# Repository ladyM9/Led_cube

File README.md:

# Led_cube(8x8x8)
This project is based on the STM32F103C8T6 (Blue Pill) for controlling WS2812D (LED diodes). The LED cube is used for ambient lighting.
Various animations can be displayed on the LED cube, which makes it very impressive and interesting.

## ***How this project works***

The STM32F103C8T6 and WS2812D (LED diodes) cannot be directly connected because they operate at different voltage levels. 
To solve this issue, the LED diodes and STM32F103C8T6 are connected using a logic level converter. A computer power supply is used to power the LED cube.
It is necessary to use a computer power supply because when all 512 LEDs are lit, the LED cube requires a 20 A/5 V power source to function correctly.
Programming code upload on STM32F103C8T6 with ST-Link.

## ***Contents of repo***
- Programming code for controlling the LED cube
- 3D design of the stand for the Led cube
- PCB for the Led cube(It is currently being created)
- Images of the Led cube

## ***Commponets for project:***
- STM32F103C8T6
- ST-Link
- WS2812D(512 piece)
- Capacitors(100 nF)
- Power supply(20A/5V)
- Logic Level Converter
- Wires for BreadBoard
- 3D printer(optional)
- 3D printing filament

<p align="center">
  
 <br>
    <b>View of the Led cube and the 3d print stand</b>
</p>
<br>

<p align="center">
  
 <br>
    <b>Overview when all leds diodes working</b>
</p>
<br>

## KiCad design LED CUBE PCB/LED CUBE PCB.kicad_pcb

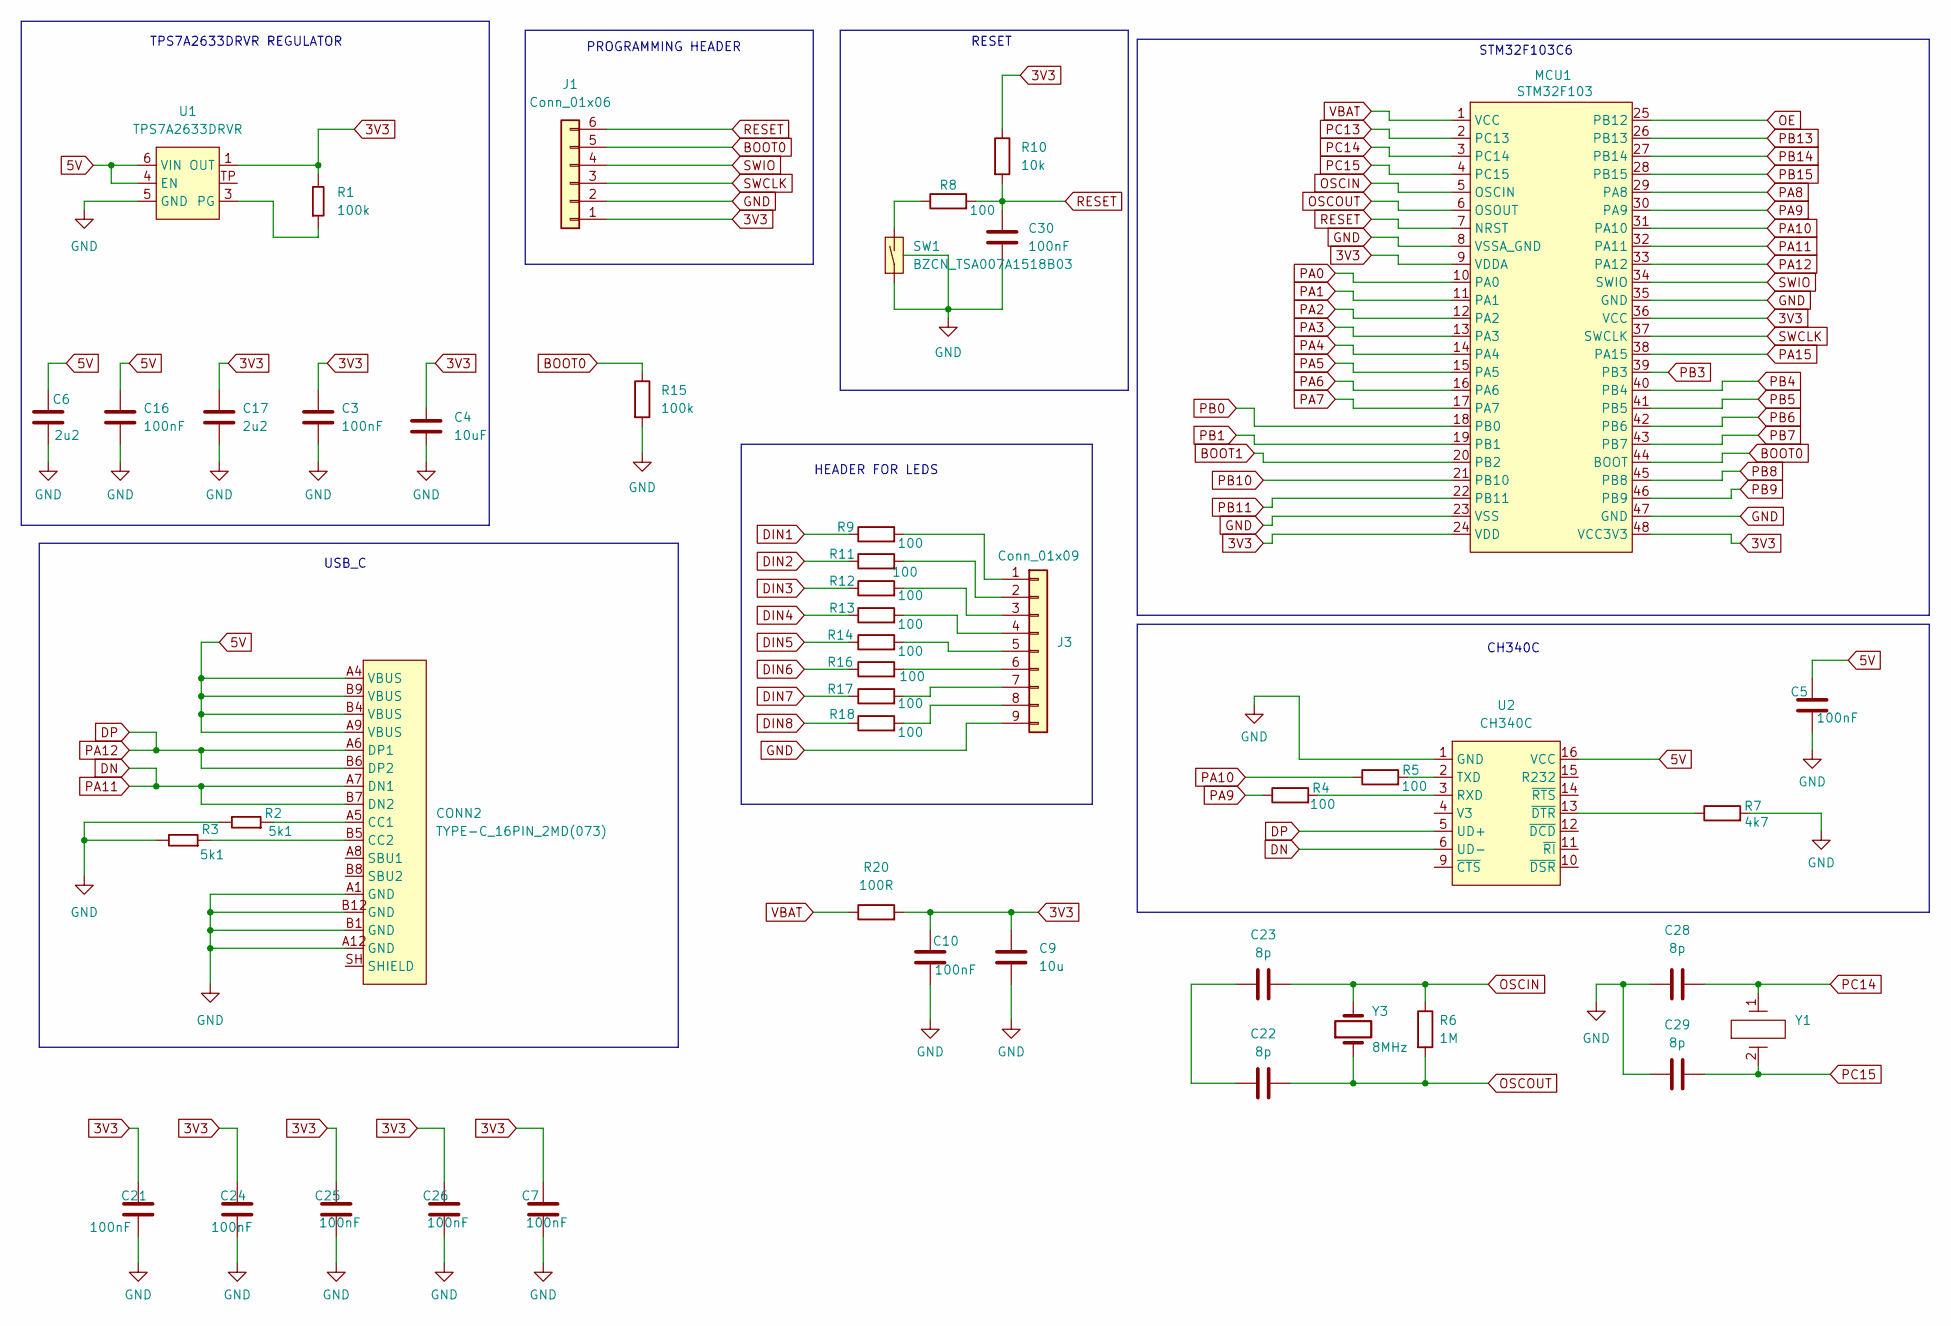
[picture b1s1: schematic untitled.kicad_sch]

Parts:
C3, C5, C7, C10, C16, C21, C24, C25, C26: 100nF; C0603
C4: 10uF; C1206
C6, C17: 2u2; C0603
C9: 10u; C1206
C22, C23, C28, C29: 8p; C0603
C30: 100nF; R0603
CONN2: TYPE-C_16PIN_2MD(073)
J1: Conn_01x06; PinHeader_1x06_P2.54mm_Vertical
J3: Conn_01x09; PinHeader_1x09_P2.54mm_Vertical
MCU1: STM32F103; TQFP48
R1, R15: 100k; R0603
R2, R3: 5k1; R0603
R4, R5, R8, R9, R11, R12, R13, R14, R16, R17, R18: 100; R0603
R6: 1M; R1206
R7: 4k7; R0603
R10: 10k; R0603
R20: 100R; R0603
SW1: BZCN_TSA007A1518B03; TSA007A1518B03
U1: TPS7A2633DRVR; WSON-6
U2: CH340C; SOP-16
Y1: SMD3215-2P
Y3: 8MHz; ECS-080-18-23G-JGN-TR

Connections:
3V3: C3.1, C4.2, C7.1, C9.2, C10.1, C17.1, C21.1, C24.1, C25.1, C26.1, J1.1, MCU1.9 (VDDA), MCU1.24 (VDD), MCU1.36 (VCC), MCU1.48 (VCC3V3), R1.2, R10.1, R20.2, U1.1 (OUT); also elsewhere on the board
5V: C5.1, C6.1, C16.1, CONN2.A4 (VBUS), CONN2.A9 (VBUS), CONN2.B4 (VBUS), CONN2.B9 (VBUS), U1.4 (EN), U1.6 (VIN), U2.16 (VCC); also elsewhere on the board
BOOT0: J1.5, MCU1.44 (BOOT), R15.1
BOOT1: MCU1.20 (PB2)
DIN1: R9.1; also elsewhere on the board
DIN2: R11.1; also elsewhere on the board
DIN3: R12.1; also elsewhere on the board
DIN4: R13.1; also elsewhere on the board
DIN5: R14.1; also elsewhere on the board
DIN6: R16.1; also elsewhere on the board
DIN7: R17.1; also elsewhere on the board
DIN8: R18.1; also elsewhere on the board
DN: CONN2.A7 (DN1), CONN2.B7 (DN2), MCU1.32 (PA11), U2.6 (UD-)
DP: CONN2.A6 (DP1), CONN2.B6 (DP2), MCU1.33 (PA12), U2.5 (UD+)
GND: C3.2, C4.1, C5.2, C6.2, C7.2, C9.1, C10.2, C16.2, C17.2, C21.2, C24.2, C25.2, C26.2, C28.1, C29.1, C30.2, CONN2.A1 (GND), CONN2.A12 (GND), CONN2.B1 (GND), CONN2.B12 (GND), J1.2, J3.9, MCU1.8 (VSSA_GND), MCU1.23 (VSS), MCU1.35 (GND), MCU1.47 (GND), R2.2, R3.2, R7.2, R15.2, SW1.1 (SW1), SW1.PAD, U1.5 (GND), U2.1 (GND); also elsewhere on the board
unnamed: C22.2, C23.2
unnamed: CONN2.A5 (CC1), R2.1
unnamed: CONN2.B5 (CC2), R3.1
unnamed: J3.1, R9.2
unnamed: J3.2, R11.2
unnamed: J3.3, R12.2
unnamed: J3.4, R13.2
unnamed: J3.5, R14.2
unnamed: J3.6, R16.2
unnamed: J3.7, R17.2
unnamed: J3.8, R18.2
unnamed: R8.1, SW1.2 (SW2)
unnamed: R1.1, U1.3 (PG)
unnamed: R4.2, U2.3 (RXD)
unnamed: R5.2, U2.2 (TXD)
unnamed: R7.1, U2.13 (~DTR)
OE: MCU1.25 (PB12); also elsewhere on the board
OSCIN: C23.1, MCU1.5 (OSCIN), R6.1, Y3.2
OSCOUT: C22.1, MCU1.6 (OSOUT), R6.2, Y3.1
PA0: MCU1.10 (PA0); also elsewhere on the board
PA1: MCU1.11 (PA1)
PA2: MCU1.12 (PA2)
PA3: MCU1.13 (PA3)
PA4: MCU1.14 (PA4)
PA5: MCU1.15 (PA5)
PA6: MCU1.16 (PA6)
PA7: MCU1.17 (PA7)
PA8: MCU1.29 (PA8)
PA9: MCU1.30 (PA9), R4.1
PA10: MCU1.31 (PA10), R5.1
PA15: MCU1.38 (PA15)
PB0: MCU1.18 (PB0); also elsewhere on the board
PB1: MCU1.19 (PB1)
PB3: MCU1.39 (PB3)
PB4: MCU1.40 (PB4); also elsewhere on the board
PB5: MCU1.41 (PB5); also elsewhere on the board
PB6: MCU1.42 (PB6); also elsewhere on the board
PB7: MCU1.43 (PB7); also elsewhere on the board
PB8: MCU1.45 (PB8); also elsewhere on the board
PB9: MCU1.46 (PB9); also elsewhere on the board
PB10: MCU1.21 (PB10)
PB11: MCU1.22 (PB11)
PB13: MCU1.26 (PB13)
PB14: MCU1.27 (PB14)
PB15: MCU1.28 (PB15)
PC13: MCU1.2 (PC13)
PC14: C28.2, MCU1.3 (PC14), Y1.1
PC15: C29.2, MCU1.4 (PC15), Y1.2
RESET: C30.1, J1.6, MCU1.7 (NRST), R8.2, R10.2
SWCLK: J1.3, MCU1.37 (SWCLK)
SWIO: J1.4, MCU1.34 (SWIO)
VBAT: MCU1.1 (VCC), R20.1

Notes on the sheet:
RESET
TPS7A2633DRVR REGULATOR
STM32F103C6
HEADER FOR LEDS
PROGRAMMING HEADER
USB_C
CH340C

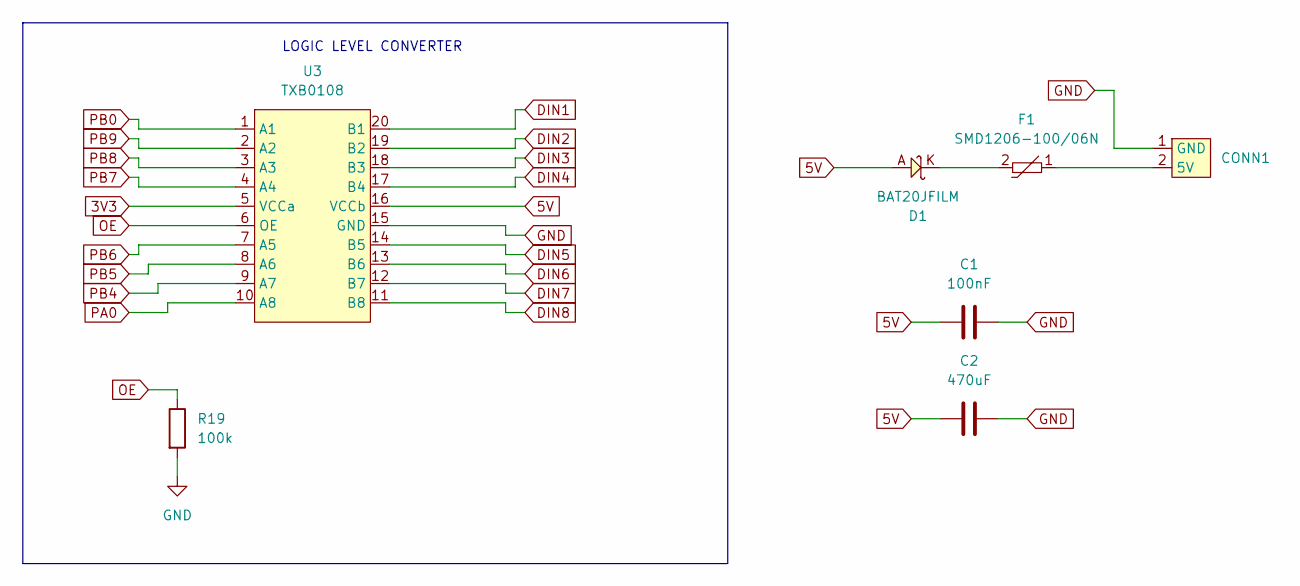
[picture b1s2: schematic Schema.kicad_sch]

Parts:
C1: 100nF; C0603
C2: 470uF; C0603
CONN1: POWER_SUPPLY; PinSocket_1x02_P2.54mm_Vertical
D1: BAT20JFILM; SOD323
F1: SMD1206-100/06N; 1206
R19: 100k; R0603
U3: TXB0108

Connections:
3V3: U3.5 (VCCa); also elsewhere on the board
5V: C1.2, C2.2, D1.A, U3.16 (VCCb); also elsewhere on the board
DIN1: U3.20 (B1); also elsewhere on the board
DIN2: U3.19 (B2); also elsewhere on the board
DIN3: U3.18 (B3); also elsewhere on the board
DIN4: U3.17 (B4); also elsewhere on the board
DIN5: U3.14 (B5); also elsewhere on the board
DIN6: U3.13 (B6); also elsewhere on the board
DIN7: U3.12 (B7); also elsewhere on the board
DIN8: U3.11 (B8); also elsewhere on the board
GND: C1.1, C2.1, CONN1.1 (GND), R19.2, U3.15 (GND); also elsewhere on the board
unnamed: CONN1.2 (5V), F1.1
unnamed: D1.K, F1.2
OE: R19.1, U3.6 (OE); also elsewhere on the board
PA0: U3.10 (A8); also elsewhere on the board
PB0: U3.1 (A1); also elsewhere on the board
PB4: U3.9 (A7); also elsewhere on the board
PB5: U3.8 (A6); also elsewhere on the board
PB6: U3.7 (A5); also elsewhere on the board
PB7: U3.4 (A4); also elsewhere on the board
PB8: U3.3 (A3); also elsewhere on the board
PB9: U3.2 (A2); also elsewhere on the board

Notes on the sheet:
LOGIC LEVEL CONVERTER

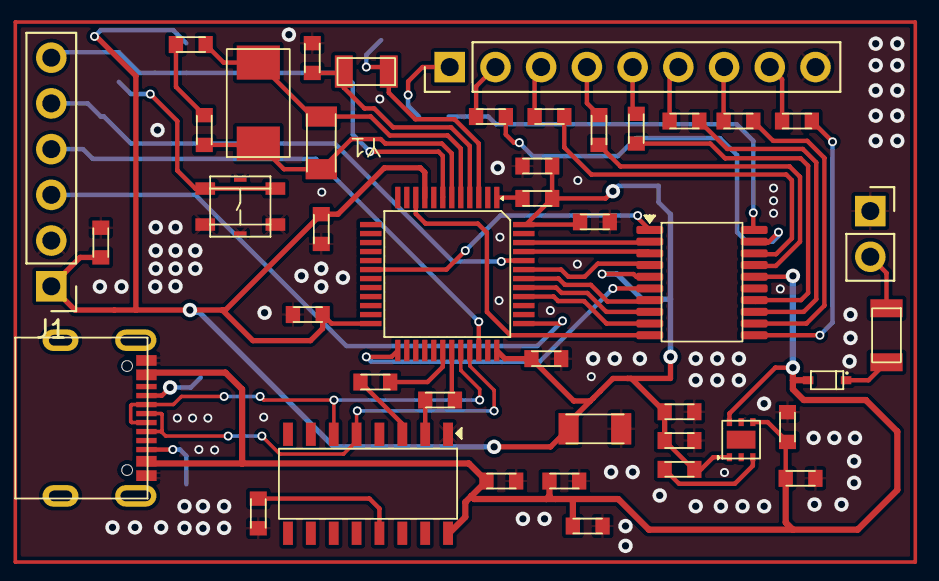
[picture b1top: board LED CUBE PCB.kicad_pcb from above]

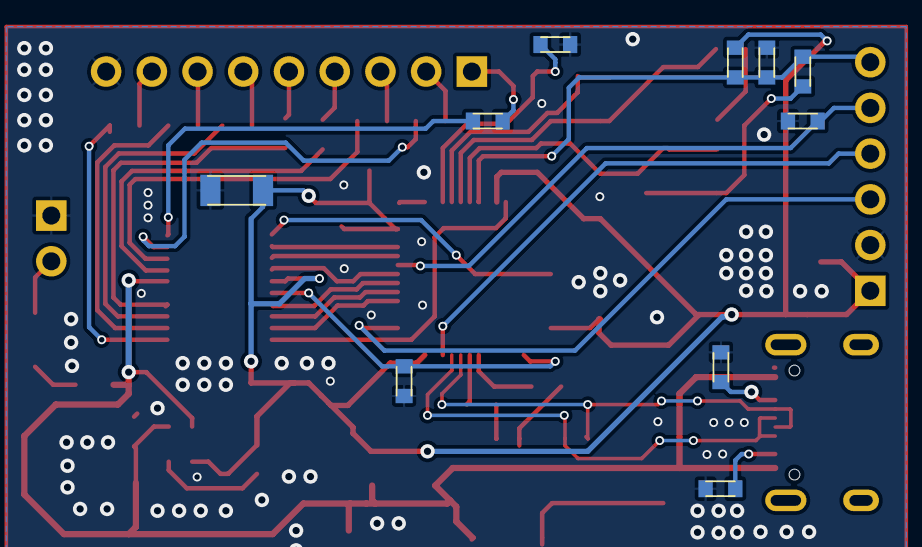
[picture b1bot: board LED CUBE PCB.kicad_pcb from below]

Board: 2 copper layers, 53 parts (10 on the bottom side), 51 nets.

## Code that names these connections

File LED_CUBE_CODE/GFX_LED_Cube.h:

#ifndef __ADAFRUIT_GFX_CUBE_H__
#define __ADAFRUIT_GFX_CUBE_H__

#if ARDUINO >= 100
 #include "Arduino.h"
#else
 #include "WProgram.h"
#endif

#include <Adafruit_NeoPixel.h>
#include <Adafruit_GFX.h>

#define PIN1        PB0 // Connected to D2
#define PIN2        PB9 // Connected to D3
#define PIN3        PB8 // Connected to D4
#define PIN4        PB7 // Connected to D5
#define PIN5        PB6 // Connected to D6
#define PIN6        PB5 // Connected to D7
#define PIN7        PB4 // Connected to D8
#define PIN8        PA0 // Connected to D9
#define NUMPIXELS 	64 // How many LEDs there are on one layer
#define LAYERS		8

class LEDCube : public Adafruit_GFX {
	public:
	LEDCube();

  	void begin(void);
  	void clear(void);
  	void display(void);
  	void drawPixel(int16_t x, int16_t y, uint16_t color);
	void drawPixel_2(int16_t a, int16_t b, uint16_t color);
	void drawPixel_3(int16_t x1, int16_t y1, uint16_t color);
	void setDepth(int _d);
	void setDepth_2(int _d2);
	void setDepth_3(int _d3);

	private:
	Adafruit_NeoPixel *pixels[8];
	int _depth = 0;
	int _depth2 = 8;
	int _depth3 = 0;

};

#endif

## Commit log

2022-05-11 Create My models in Free Cad
2022-05-11 Create My Free CAD models
2022-05-29 Cooling mesh fixed on Desni donji dio led_cube.FCStd
2022-06-03 Nije chamfer napravljen do kraja, fale utori za pleksiglas, i nedostaje utor na donjoj strani
2022-06-04 Lijevi donji dio pregledat utore za konektore
2022-06-05 STM32 holder change, header and XT90 connector hole size change
2022-07-26 Tool za prepravak razmaka, prva verzija
2022-07-27 Verzija 2
2022-07-28 Changed hole size for LED Tool.
2022-07-30 Added cylinder around LED (for easier soldering).
2022-08-06 Added holder for 8 LEDs (tool for 8 LEDs)
2022-08-08 Changed distance between LEDs (from 35mm to 33.33mm)
2022-08-13 Added 3D printed feets
    NOTE: Use TPU material, no retraction fore feets.
2022-08-17 Prvi kod za led cube, neopixel example ustvari
2022-08-18 Uspješno prvo nijansiranje boja ali samo na prvom layeru, odnosno na 64 ledice, nijansirana je plava boja
2022-08-19 Upgrade nijansiranja, sada se boje mijenjaju kroz cijeli prvi layer, ledice periodički mijenjaju boju
2022-08-24 Prikaz 9 slova na led cube-u, dodan library koji povezuje NeoPixel i NeoMatrix
2022-08-25 Na kocki se mijenja kvadrat i slovo
2022-08-26 Dodano više različitih oblika koje se prikazuju pojedinačno na led kocki
2022-08-29 Optimizacija timera, animacije se stalno mijenjaju na led kocki zbog pravilnog korištenja timera i intervala
2022-08-30 Dodane animacije za slova, ali ne radi
2022-08-31 Ispisivanje moguće na dvije plohe led kocke, dodane još dvije animacije
2022-09-02 Boje su sređene, nisu više 16 bita nego 32, dodana još jedna animacija
2022-09-12 Dodani komentari u programski kod
2023-10-16 Files distributed in folders
2024-01-07 Added file with images
2024-01-07 Created README
2024-01-08 Added pictures of led_cube
2024-01-12 Deleted drawPixel_2, drawPixel_3 method, setDepht_2 and _3 method
2024-01-16 PCB for LED_CUBE
2024-01-16 Added setPlane method in GFX_LED_CUBE.cpp
2024-01-19 Added shema and footprints
2024-01-24 Added header and global labels
2024-05-14 Added logic level converter
2024-10-02 Push changes
2024-10-02 Deleted one double file
2024-10-02 Deleted two CAD files
2024-10-17 Cleaning up the code by removing unnecessary lines of code.
2025-11-18 Fixed problems on schematic
2025-11-18 Update schema
2025-11-19 Update PCB
2025-11-19 Added filtering for power supply
2025-11-19 Change voltage regulator
2025-11-20 Connected voltage regulator and logic level converter
2025-11-21 Added USB C and CH340C
2025-11-22 Corrected schema after review by Borna (Marina)
2025-11-23 Replaced symbol for TXB and STM
2025-11-24 Added fuse and bat20
2025-11-25 Corrected RC filter(Marina)
2025-11-25 Schema is finished
2025-11-26 I don t know what is that
2025-11-26 Beginning PCB layout
2025-11-28 Updated routing PCB
2025-11-30 Change footprint for capacitors and routing PCB
2025-12-01 Change footprint for crystal
2025-12-02 I don t know
2025-12-02 Updated PCB
2025-12-04 Added ground filled zone on PCB
2025-12-06 Problem with GND
2025-12-06 Updated PCB - Marina
2025-12-07 PCB is finish
2025-12-07 PCB is finished
2025-12-09 Solved problem with VCC3V3 and 3V3 on schematic
